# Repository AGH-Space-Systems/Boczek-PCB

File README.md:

# Boczek-PCB
 5.8 GHz 1 W radio beacon that fits on a Li-Ion battery holder
Place libaries from "project specific libaries" in your libaries folder.
AlexRF has the filter, SamacSys_Parts the ICs.

RF PA:
https://www.mouser.pl/ProductDetail/Qorvo/RFPA5542BTR13?qs=u4fy%2FsgLU9OIcUWfOD%252Bf6g%3D%3D

3.3V LDO
https://www.mouser.pl/ProductDetail/Microchip-Technology/MIC94310-SYM5-TR?qs=U6T8BxXiZAWNaMNWfdoYvQ%3D%3D

2.2 2.5 75 3.2 × 2.5 × 1.2 HMME32251B--2R2MS CYNTEC
Coils
Have to handle 2.5A of peak switch current!
https://www.mouser.pl/ProductDetail/Laird-Performance-Materials/TYS40304R7M-10?qs=cCJXSq33DME5rIwYhom2LA%3D%3D

https://www.mouser.pl/datasheet/2/597/lps4018-270702.pdf

PCB (very important for the stripline filter to work!)
JLC04161H-7628 Stackup

BOM comming soon...

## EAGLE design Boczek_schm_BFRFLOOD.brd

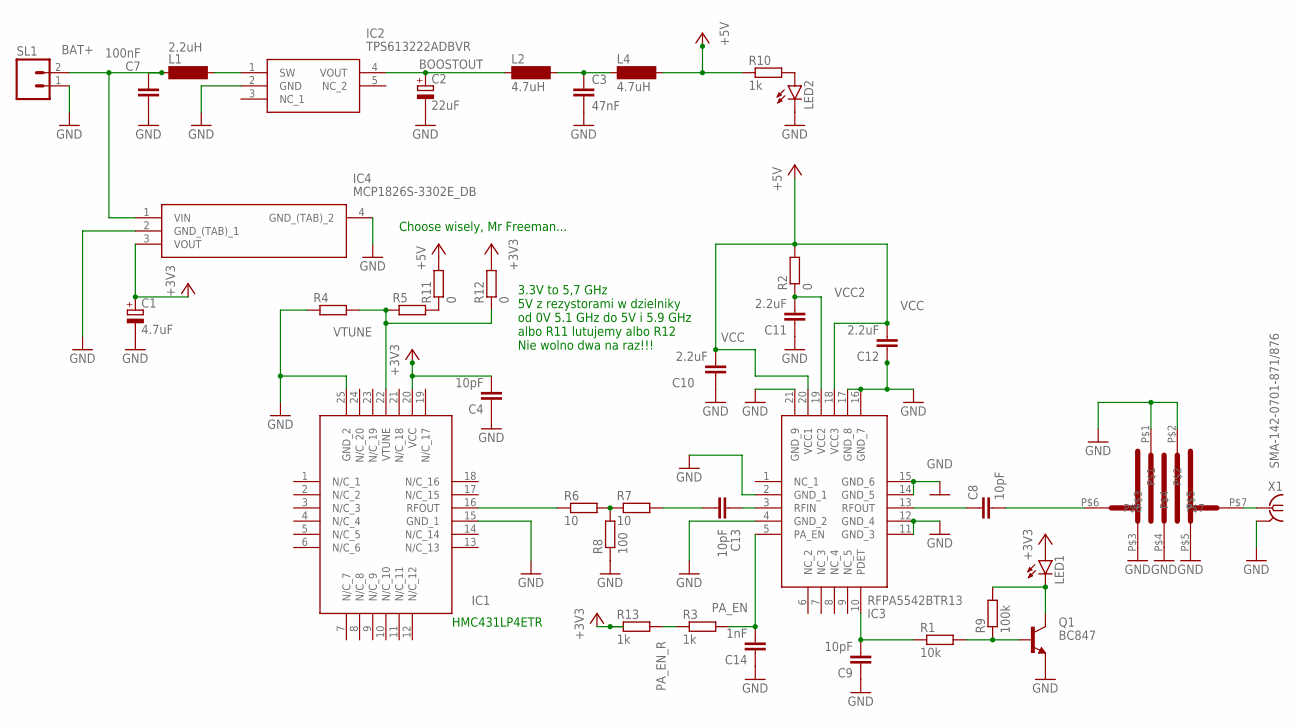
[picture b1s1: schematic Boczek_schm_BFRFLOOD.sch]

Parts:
C1: 4.7uF; SMC_E
C2: 22uF; SMC_E
C3: 47nF; C1206
C4: 10pF; C0603
C7: 100nF; C1206
C8, C9, C13: 10pF; C0402
C10, C11, C12: 2.2uF; C0402
C14: 1nF; C0402
FL1: INTERDIGITAL_FILTER_5TH_ORDER; JLC7628_4900-5500_FILTER
IC1: HMC430LP4ETR; QFN50P400X400X100-25N; MANUFACTURER_PART_NUMBER HMC431LP4ETR
IC2: TPS613222ADBVR; SOT95P280X145-5N
IC3: RFPA5542BTR13; QFN50P400X400X85-21N
IC4: MCP1826S-3302E_DB; SOT230P700X180-4N
L1: 2.2uH; SM-NE45
L2, L4: 4.7uH; SM-NE45
LED1, LED2: LEDSMT1206; 1206
Q1: BC847; SOT23
R1: 10k; R0603
R2, R11, R12: 0; R0603
R3, R10, R13: 1k; R0603
R4, R5: R-EU_R0603; R0603
R6, R7: 10; R0603
R8: 100; R0603
R9: 100k; R0603
SL1: M02; 02P
X1: SMA-142-0701-871/876; J502-ND-142-0701-871/876

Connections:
+3V3: C1.+, C4.2, IC1.20 (VCC), IC4.3 (VOUT), LED1.A, R12.2, R13.1
+5V: L4.2, R10.1, R11.2
BAT+: C7.2, IC4.1 (VIN), L1.1, SL1.2
BOOSTOUT: C2.+, IC2.4 (VOUT), L2.1
GND: C1.-, C2.-, C3.2, C4.1, C7.1, C9.1, C10.1, C11.1, C12.1, C14.1, FL1.P$1, FL1.P$2, FL1.P$3, FL1.P$4, FL1.P$5, IC1.15 (GND_1), IC1.25 (GND_2), IC2.2 (GND), IC3.2 (GND_1), IC3.4 (GND_2), IC3.11 (GND_3), IC3.12 (GND_4), IC3.14 (GND_5), IC3.15 (GND_6), IC3.16 (GND_7), IC3.17 (GND_8), IC3.21 (GND_9), IC4.2 (GND_(TAB)_1), IC4.4 (GND_(TAB)_2), LED2.C, Q1.2 (E), R4.1, R8.1, SL1.1, X1.G@1 (2), X1.G@2 (2), X1.G@3 (2), X1.G@4 (2)
unnamed: FL1.P$7, X1.1
unnamed: IC1.16 (RFOUT), R6.1
unnamed: R6.2, R7.1, R8.2
unnamed: C13.1, IC3.3 (RFIN)
unnamed: LED2.A, R10.2
unnamed: C8.2, FL1.P$6
unnamed: IC2.1 (SW), L1.2
unnamed: C13.2, R7.2
unnamed: C9.2, IC3.10 (PDET), R1.1
unnamed: LED1.C, Q1.3 (C), R9.2
unnamed: C3.1, L2.2, L4.1
unnamed: Q1.1 (B), R1.2, R9.1
unnamed: C8.1, IC3.13 (RFOUT)
unnamed: R5.2, R11.1
PA_EN: C14.2, IC3.5 (PA_EN), R3.2
PA_EN_R: R3.1, R13.2
VCC: C10.2, C12.2, IC3.18 (VCC3), IC3.20 (VCC1), R2.2
VCC2: C11.2, IC3.19 (VCC2), R2.1
VTUNE: IC1.22 (VTUNE), R4.2, R5.1, R12.1

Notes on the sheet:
HMC431LP4ETR
Choose wisely, Mr Freeman...
3.3V to 5,7 GHz 5V z rezystorami w dzielniky od 0V 5.1 GHz do 5V i 5.9 GHz albo R11 lutujemy albo R12 Nie wolno dwa na raz!!!

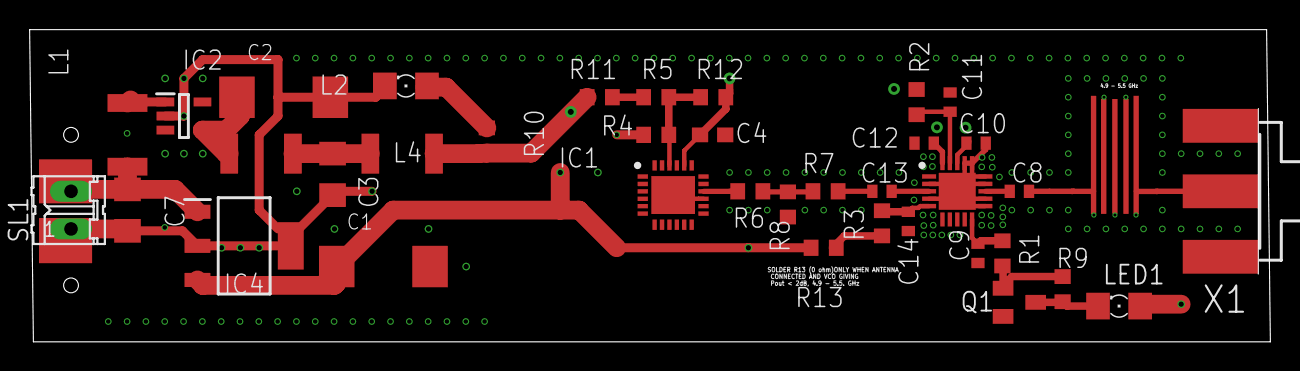
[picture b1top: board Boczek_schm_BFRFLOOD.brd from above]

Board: 4 copper layers, 83.7 x 21.1 mm, 38 parts (0 on the bottom side), 24 nets.

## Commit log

2023-09-08 Removing unused files
2023-09-09 Grand update, BOM for two devices
    WE MAKING OUT OF BETA WITH THIS ONE 🗣🗣🗣🔥🔥🥶🥶
    -Completed BOM, board and schematic
    -Unified element usage (all resistors now 0803)
    -Rearanged the VCO tuning resistors, so that illegal combinations (R5 and R12)
    -Added startup and assembly instruction on the board and in the schematic (don't be scared, it's Polish)
    -redid the output filter to match the frequncy span. It's now 3 element and uses a different response curve, giving lower loss, about 1 dB in passband
2023-09-22 Gerbers added (Final production commit???)
    Added gerbers, nothing else changed.
